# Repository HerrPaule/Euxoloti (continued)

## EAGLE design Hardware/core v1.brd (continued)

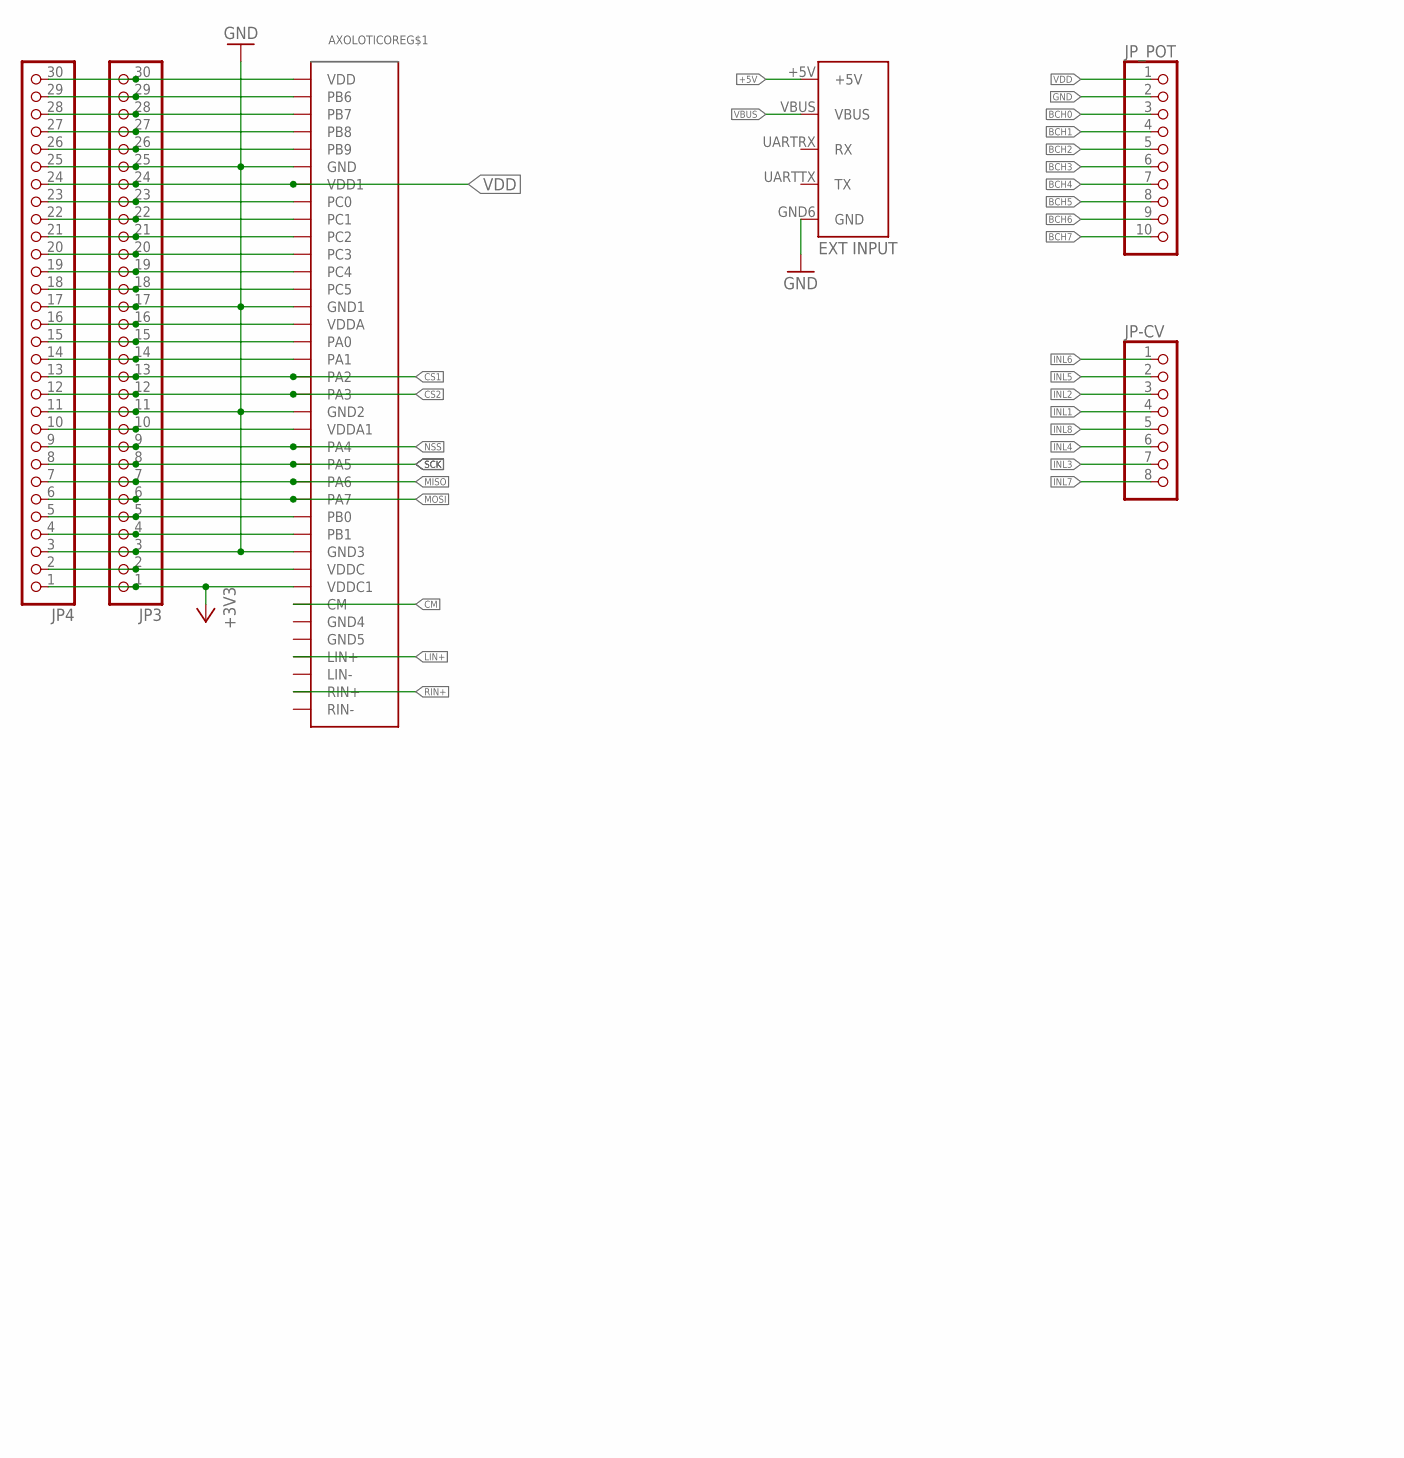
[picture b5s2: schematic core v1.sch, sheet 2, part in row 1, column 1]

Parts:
AXOLOTICORE: AXOLOTI-CORE
JP3, JP4: PINHD-1X30; 1X30
JP-CV: PINHD-1X8_2.54; 1X08
JP_POT: PINHD-1X10; 1X10

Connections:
+3V3: AXOLOTICORE.VDDC1, JP3.1, JP4.1; also elsewhere on the board
+5V: AXOLOTICORE.+5V; also elsewhere on the board
BCH0: JP_POT.3; also elsewhere on the board
BCH1: JP_POT.4; also elsewhere on the board
BCH2: JP_POT.5; also elsewhere on the board
BCH3: JP_POT.6; also elsewhere on the board
BCH4: JP_POT.7; also elsewhere on the board
BCH5: JP_POT.8; also elsewhere on the board
BCH6: JP_POT.9; also elsewhere on the board
BCH7: JP_POT.10; also elsewhere on the board
CM: AXOLOTICORE.CM; also elsewhere on the board
CS1: AXOLOTICORE.PA2, JP3.13, JP4.13; also elsewhere on the board
CS2: AXOLOTICORE.PA3, JP3.12, JP4.12; also elsewhere on the board
GND: AXOLOTICORE.GND, AXOLOTICORE.GND1, AXOLOTICORE.GND2 (GND3), AXOLOTICORE.GND3 (GND2), AXOLOTICORE.GND6 (GND), JP3.3, JP3.11, JP3.17, JP3.25, JP4.3, JP4.11, JP4.17, JP4.25, JP_POT.2; also elsewhere on the board
INL1: JP-CV.4; also elsewhere on the board
INL2: JP-CV.3; also elsewhere on the board
INL3: JP-CV.7; also elsewhere on the board
INL4: JP-CV.6; also elsewhere on the board
INL5: JP-CV.2; also elsewhere on the board
INL6: JP-CV.1; also elsewhere on the board
INL7: JP-CV.8; also elsewhere on the board
INL8: JP-CV.5; also elsewhere on the board
LIN+: AXOLOTICORE.LIN+; also elsewhere on the board
MISO: AXOLOTICORE.PA6, JP3.7, JP4.7; also elsewhere on the board
MOSI: AXOLOTICORE.PA7, JP3.6, JP4.6; also elsewhere on the board
unnamed: AXOLOTICORE.PB1, JP3.4, JP4.4
unnamed: AXOLOTICORE.PB0, JP3.5, JP4.5
unnamed: AXOLOTICORE.VDDC, JP3.2, JP4.2
unnamed: AXOLOTICORE.VDDA1, JP3.10, JP4.10
unnamed: AXOLOTICORE.PA1, JP3.14, JP4.14
unnamed: AXOLOTICORE.PA0, JP3.15, JP4.15
unnamed: AXOLOTICORE.VDDA, JP3.16, JP4.16
unnamed: AXOLOTICORE.PC5, JP3.18, JP4.18
unnamed: AXOLOTICORE.PC4, JP3.19, JP4.19
unnamed: AXOLOTICORE.PC3, JP3.20, JP4.20
unnamed: AXOLOTICORE.PC2, JP3.21, JP4.21
unnamed: AXOLOTICORE.PC1, JP3.22, JP4.22
unnamed: AXOLOTICORE.PC0, JP3.23, JP4.23
unnamed: AXOLOTICORE.PB9, JP3.26, JP4.26
unnamed: AXOLOTICORE.PB8, JP3.27, JP4.27
unnamed: AXOLOTICORE.PB7, JP3.28, JP4.28
unnamed: AXOLOTICORE.PB6, JP3.29, JP4.29
NSS: AXOLOTICORE.PA4, JP3.9, JP4.9
RIN+: AXOLOTICORE.RIN+; also elsewhere on the board
SCK: AXOLOTICORE.PA5, JP3.8, JP4.8; also elsewhere on the board
VBUS: AXOLOTICORE.VBUS; also elsewhere on the board
VDD: AXOLOTICORE.VDD1, JP3.24, JP4.24, JP_POT.1; also elsewhere on the board
VDD+: AXOLOTICORE.VDD, JP3.30, JP4.30

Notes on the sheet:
Paul 2015
contact@irieelectronics.de

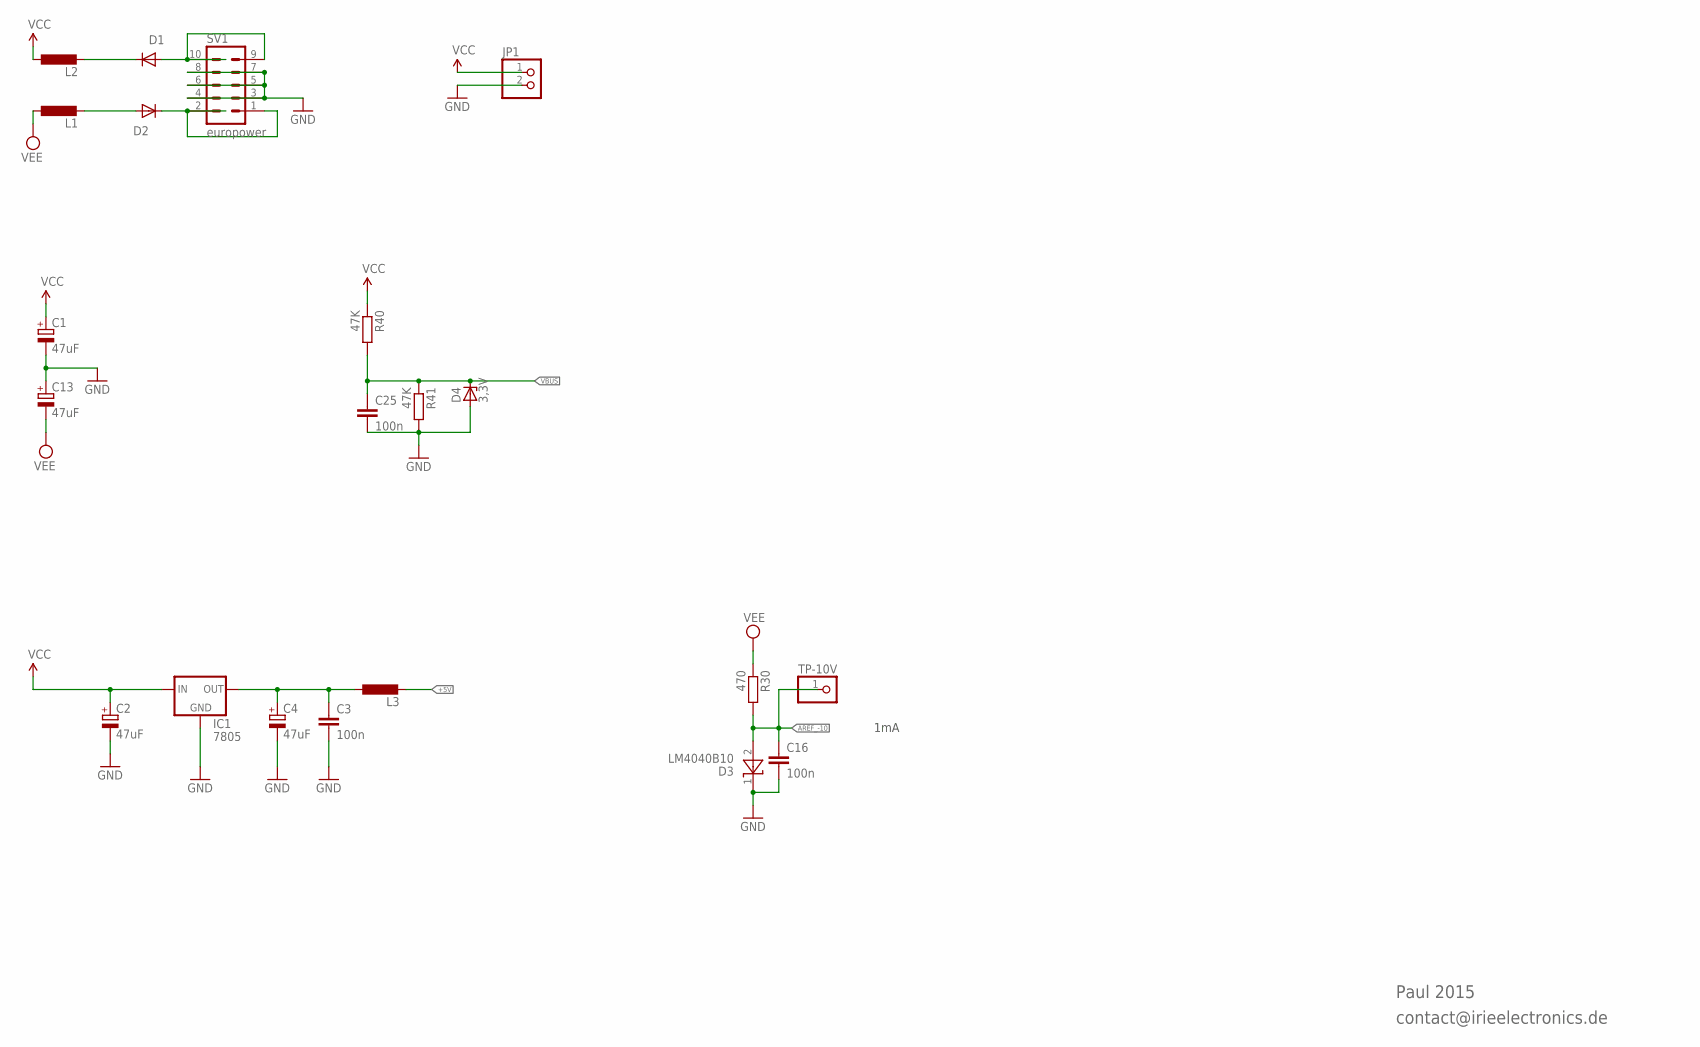
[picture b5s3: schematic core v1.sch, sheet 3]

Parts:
C1, C2, C13: 47uF; E2-5
C3, C16, C25: 100n; C025-025X050
C4: 47uF; E2,5-5
D1, D2: 1N5819HW; DO35-10
D3: LM4040B10; TO-92
D4: 3,3V; DO35Z10
IC1: 7805; 78XXS
JP1: PINHD-1X2; 1X02
L1, L2, L3: L-EU0207/10; 0207/10
R30: 470; 0207/12
R40, R41: 47K; 0207/7
SV1: europower; EURO_PWR_HEADER_FAT
TP-10V: PINHD-1X1_2.54; 1X01

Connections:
+5V: L3.2; also elsewhere on the board
+5V_RAW: C3.1, C4.+, IC1.OUT, L3.1
AREF_-10: C16.1, D3.2 (A), R30.2, TP-10V.1; also elsewhere on the board
GND: C1.-, C2.-, C3.2, C4.-, C13.+, C16.2, C25.2, D3.1 (C), D4.A, IC1.GND, JP1.2, R41.2, SV1.3, SV1.4, SV1.5, SV1.6, SV1.7, SV1.8; also elsewhere on the board
unnamed: D1.C, L2.2
unnamed: D2.A, L1.2
unnamed: D1.A, SV1.9, SV1.10
unnamed: D2.C, SV1.1, SV1.2
VBUS: C25.1, D4.C, R40.2, R41.1; also elsewhere on the board
VCC: C1.+, C2.+, IC1.IN, JP1.1, L2.1, R40.1; also elsewhere on the board
VEE: C13.-, L1.1, R30.1; also elsewhere on the board

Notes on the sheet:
1mA
Paul 2015
contact@irieelectronics.de

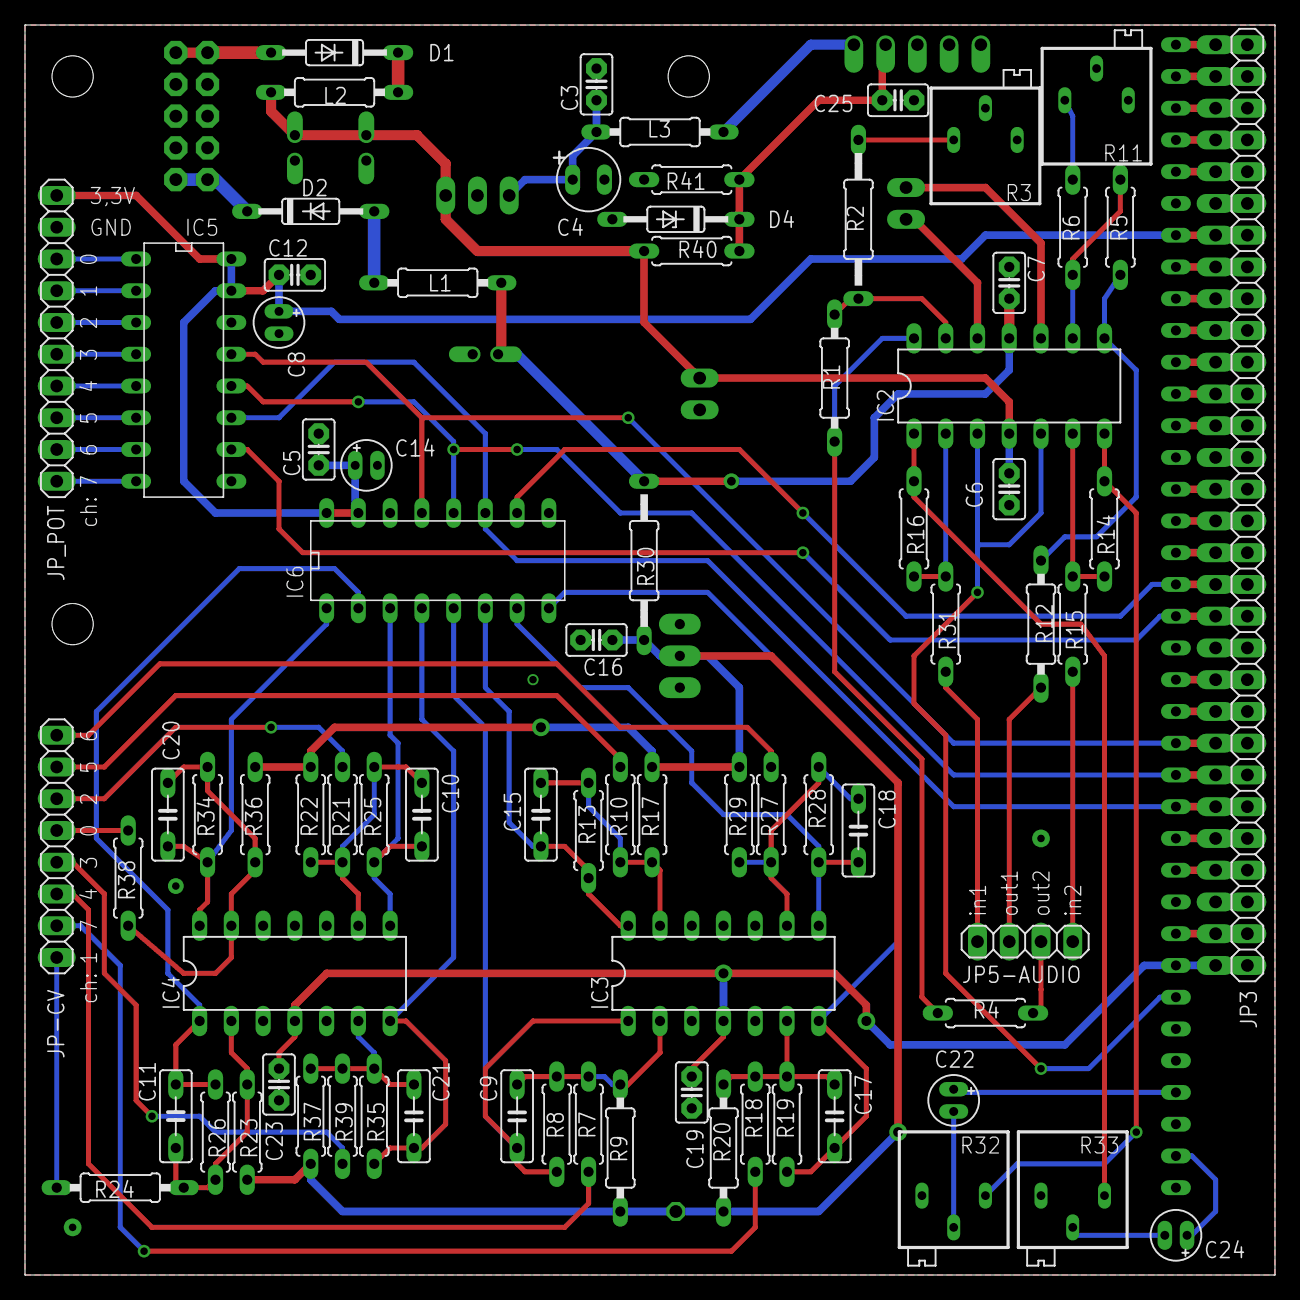
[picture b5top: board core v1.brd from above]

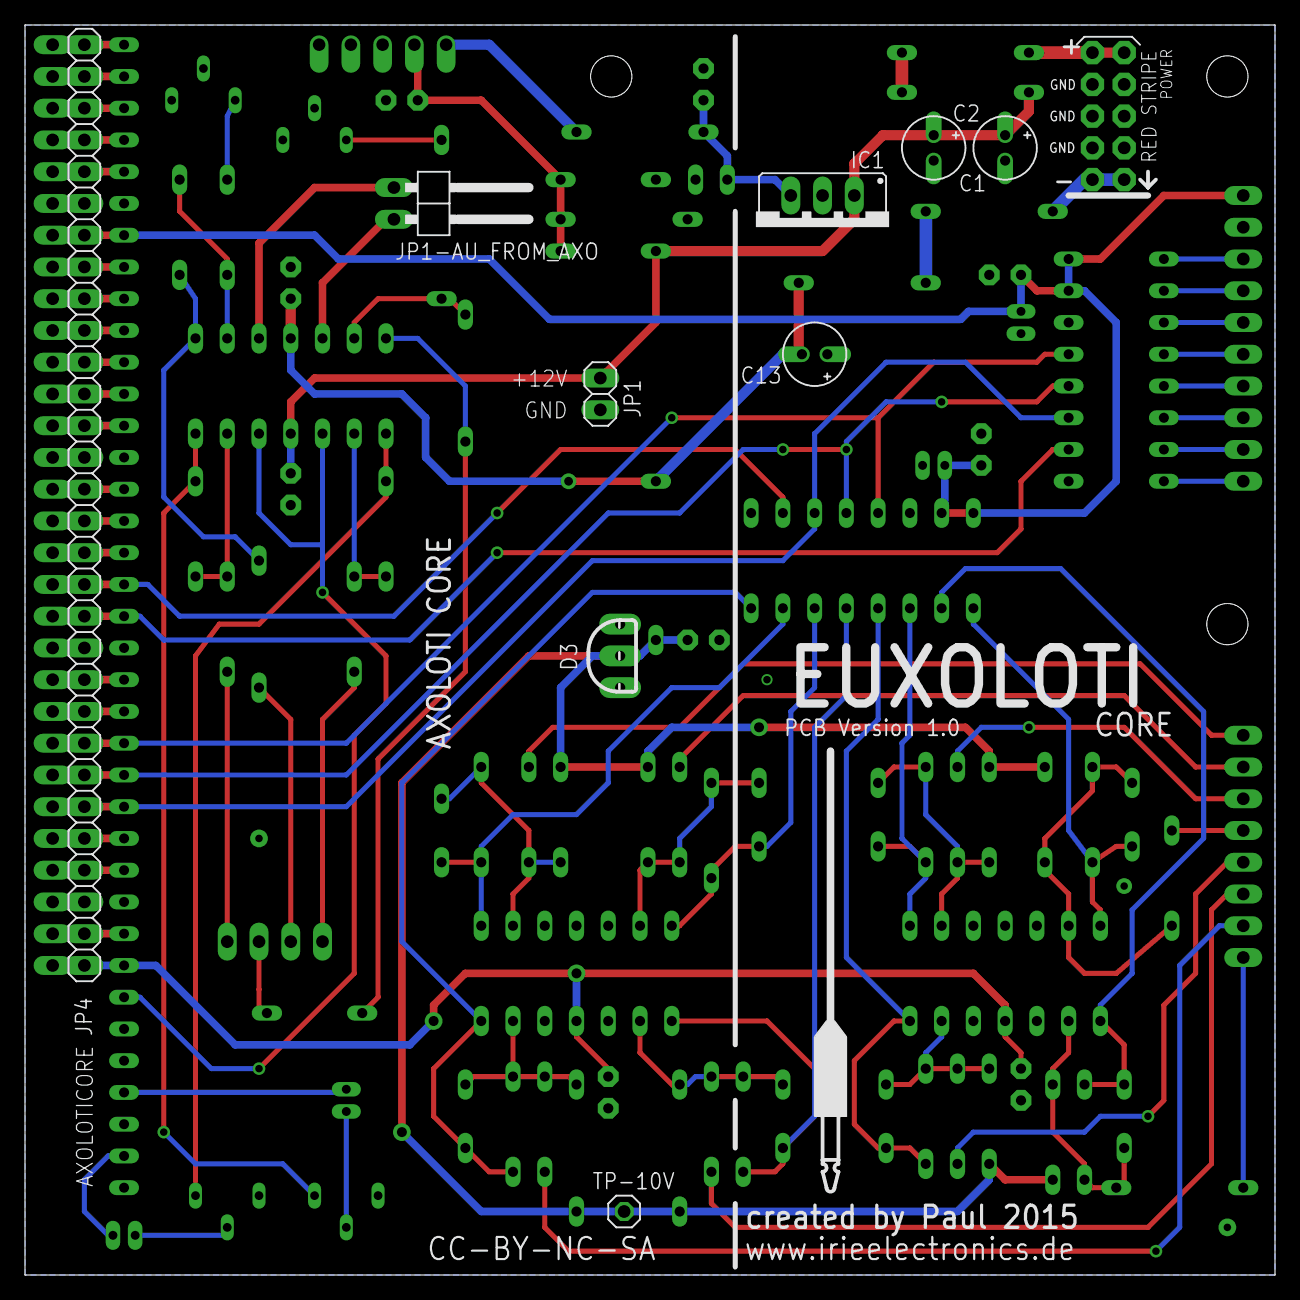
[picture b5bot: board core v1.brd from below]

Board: 4 copper layers, 100.0 x 100.0 mm, 90 parts (12 on the bottom side), 90 nets.

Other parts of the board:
U$1: KLINKENBILD

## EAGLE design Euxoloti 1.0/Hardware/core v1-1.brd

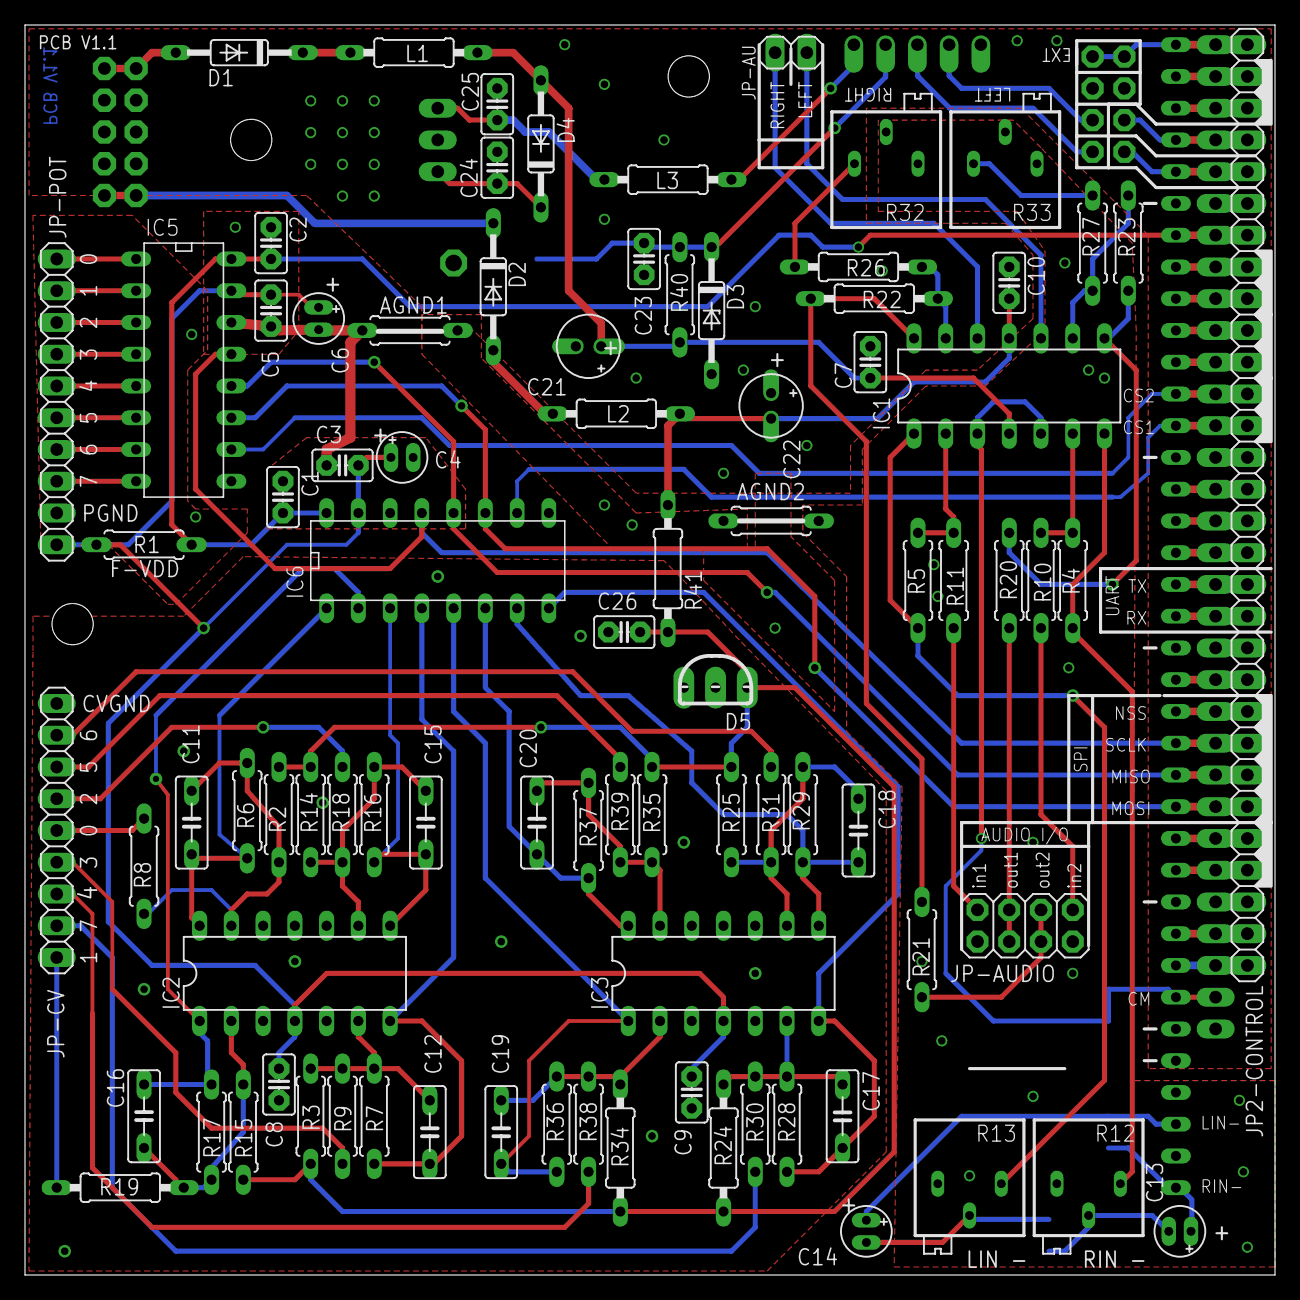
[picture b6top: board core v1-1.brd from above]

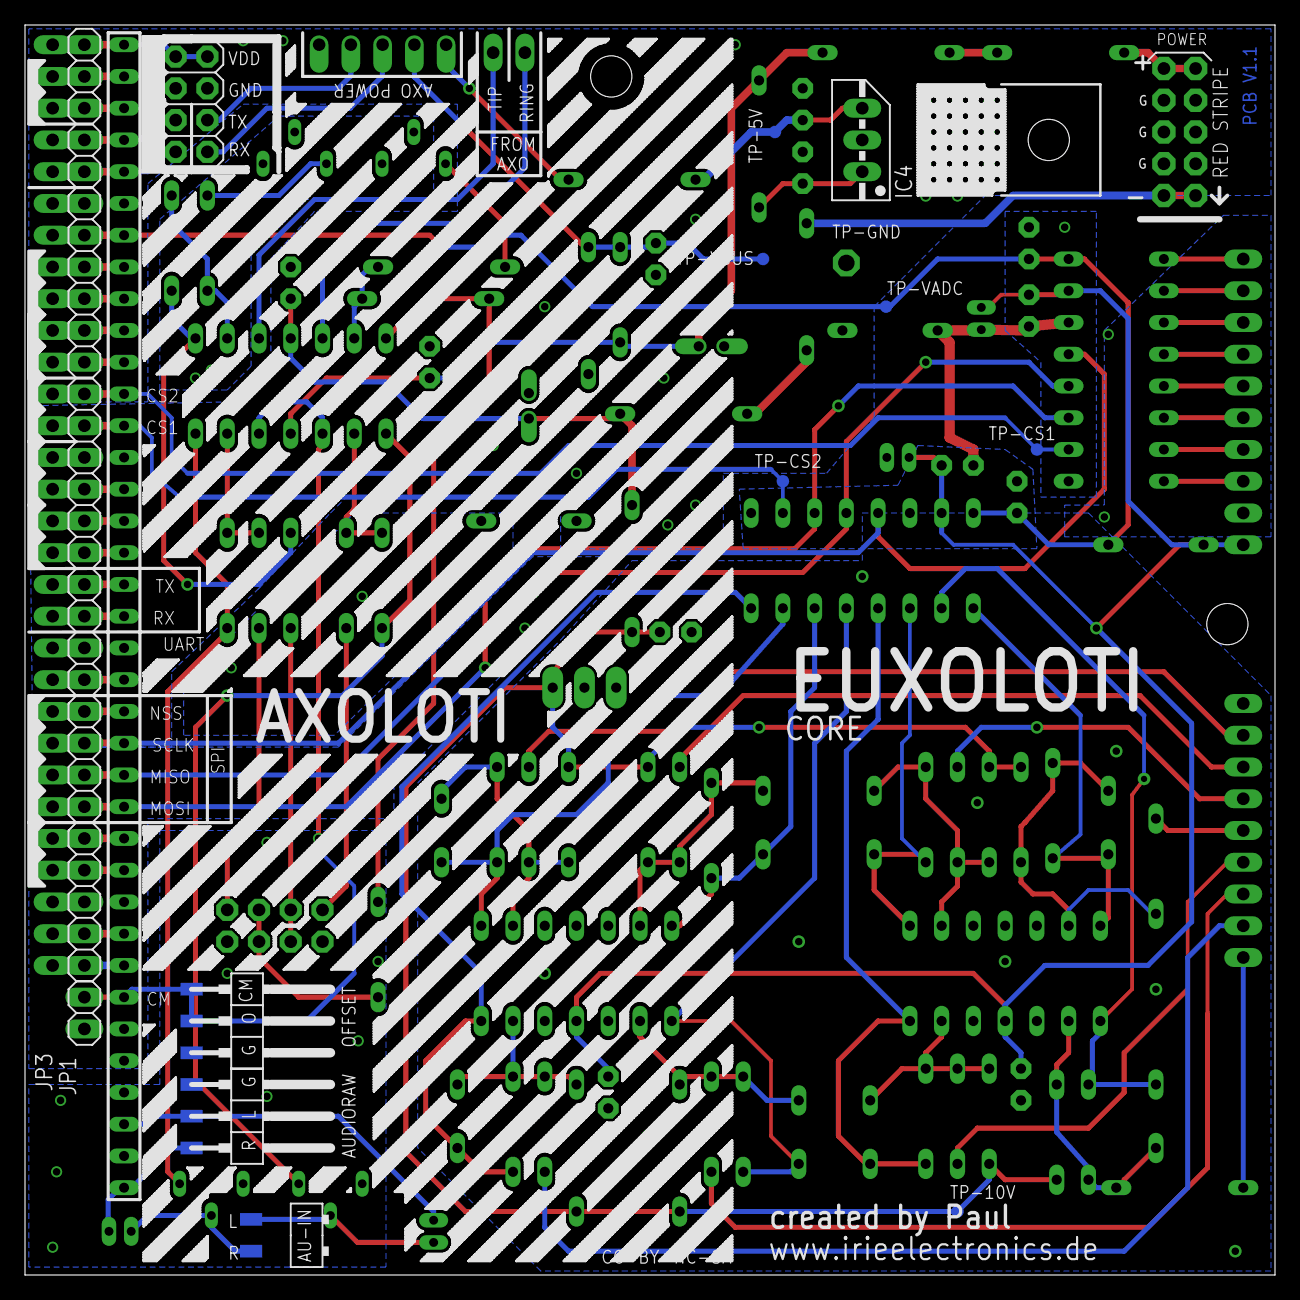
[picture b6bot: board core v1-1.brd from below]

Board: 4 copper layers, 100.0 x 100.0 mm, 104 parts (16 on the bottom side), 96 nets.

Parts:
AGND1, AGND2: 0R; 0207/7
AU-IN: 1X02SMD/90
AUDIORAW: 1X03SMD/90
AXO_CORE: AXO-CORE; AXOLOTI-CORE
BOTTOM_ARTWORK: LABEL_COREBOTTOM
C1, C2, C3, C5, C7, C8, C9, C10, C23, C25, C26: 100n; C025-025X050
C4, C6, C13, C14: 10uF; E1,8-4
C11, C12, C15, C16, C17, C18, C19, C20: 1n; C050-025X075
C21, C22: 47uF; E2-5
C24: 330n; C025-025X050
D1, D2: 1N5819; DO35-10
D3: 3,3V; DO35Z10
D4: 1N5819HW; DO35-10
D5: LM4040A10; TO-92
EXT: 2X04
IC1: TL074P; DIL14
IC2, IC3: MCP6004; DIL14
IC4: 7805; 78MXXS
JP1, JP2-CONTROL: 1X30
JP3: 1X02
JP-AU: 1X02
JP-AUDIO: 2X04
JP-CV: 1X09
JP-POT: 1X10
L1, L2, L3: 0207/10
OFFSET: 1X03SMD/90
POWER: EURO_POWER_HEADERFAT_PADS; EURO_PWR_HEADER_FAT
R1: 10R; 0207/7
R2, R3, R14, R15, R25, R35: 200k; 0207/7
R4, R5, R27: 3,3K; 0207/7
R6, R7, R16, R17, R29, R36, R37: 33K; 0207/7
R8, R9, R18, R30, R31, R38, R39: 100k; 0207/7
R10, R11, R23: 22K; 0207/7
R12, R13: 10K; RTRIM3296P
R19: 100k; 0207/10
R20, R21: 1K; 0207/7
R22: 22K; 0207/10
R24, R34: 200k; 0207/10
R26: 3,3K; 0207/10
R28: 66,5K; 0207/7
R32, R33: 5K; RTRIM3296P
R40: 47K; 0207/7
R41: 470; 0207/10
TP-5V, TP-10V: TPTP10R; TP10R
TP-CS1, TP-CS2: TPTP10R; TP10R
TP-GND: TPPAD1-13; P1-13
TP-VADC: TPTP10R; TP10R
TP-VBUS: TPTP10R; TP10R
U$1, U$2: MCP3208_DIP; MCP2308

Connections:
+3V3: AXO_CORE.VDDC1, JP1.1, JP2-CONTROL.1
+5V: AXO_CORE.+5V, L3.2
+5V_RAW: C25.1, IC4.OUT, L3.1, TP-5V.TP
AREF_-10: C26.1, D5.A, R2.2, R3.2, R14.2, R15.2, R24.2, R25.2, R34.2, R35.2, R41.2, TP-10V.TP
BCH0: JP-POT.1, U$2.P$1
BCH1: JP-POT.2, U$2.P$2
BCH2: JP-POT.3, U$2.P$3
BCH3: JP-POT.4, U$2.P$4
BCH4: JP-POT.5, U$2.P$5
BCH5: JP-POT.6, U$2.P$6
BCH6: JP-POT.7, U$2.P$7
BCH7: JP-POT.8, U$2.P$8
CH0: C11.2, IC2.14, R6.1, U$1.P$1
CH1: C15.2, IC2.8, R16.1, U$1.P$3
CH2: C12.2, IC2.7, R7.1, U$1.P$4
CH3: C16.2, IC2.1, R17.1, U$1.P$2
CH4: C18.2, IC3.8, R29.1, U$1.P$7
CH5: C17.2, IC3.7, R28.1, U$1.P$8
CH6: C19.2, IC3.1, R36.1, U$1.P$5
CH7: C20.2, IC3.14, R37.1, U$1.P$6
CM: AXO_CORE.CM, IC1.3, IC1.5, JP3.1, OFFSET.1, OFFSET.2
CS1: AXO_CORE.PC5, JP1.18, JP2-CONTROL.18, TP-CS2.TP, U$1.P$10
CS2: AXO_CORE.PC4, JP1.19, JP2-CONTROL.19, TP-CS1.TP, U$2.P$10
GND: AGND1.2, AGND2.2, AXO_CORE.GND, AXO_CORE.GND1, AXO_CORE.GND2, AXO_CORE.GND3, AXO_CORE.GND4, AXO_CORE.GND5, AXO_CORE.GND6, C7.2, C10.1, C21.-, C22.+, C23.2, C24.2, C25.2, D3.A, EXT.3, EXT.4, IC4.GND, JP1.3, JP1.11, JP1.17, JP1.25, JP2-CONTROL.3, JP2-CONTROL.11, JP2-CONTROL.17, JP2-CONTROL.25, JP3.2, POWER.3, POWER.4, POWER.5, POWER.6, POWER.7, POWER.8, TP-GND.TP
GNDA: AGND1.1, C1.1, C2.1, C3.2, C4.-, C5.2, C6.-, C8.2, C9.2, C26.2, D5.C, IC2.3, IC2.5, IC2.10, IC2.11, IC2.12, IC3.3, IC3.5, IC3.10, IC3.11, IC3.12, JP-CV.1, JP-POT.9, U$1.P$9, U$1.P$14, U$2.P$9, U$2.P$14
GNDB: AGND2.1, AUDIORAW.1, JP-AUDIO.2, JP-AUDIO.8, OFFSET.3, R12.1, R13.1, R32.1, R32.2, R33.1, R33.2
IN1: JP-AUDIO.1, R10.2
IN2: JP-AUDIO.7, R11.2
INL1: JP-CV.5, R8.2
INL2: JP-CV.4, R18.2
INL3: JP-CV.8, R30.2
INL4: JP-CV.7, R38.2
INL5: JP-CV.3, R39.2
INL6: JP-CV.2, R31.2
INL7: JP-CV.9, R19.2
INL8: JP-CV.6, R9.2
LIN-: AUDIORAW.2, AXO_CORE.LIN-, C14.+
MIDI/RX: AXO_CORE.UARTRX, EXT.8
MIDI/TX: AXO_CORE.UARTTX, EXT.6
MISO: AXO_CORE.PA6, JP1.7, JP2-CONTROL.7, U$1.P$12, U$2.P$12
MOSI: AXO_CORE.PA7, JP1.6, JP2-CONTROL.6, U$1.P$11, U$2.P$11
unnamed: D1.C, L1.2
unnamed: C15.1, IC2.9, R14.1, R16.2, R18.1
unnamed: D2.A, L2.2
unnamed: R26.2, R32.3
unnamed: C16.1, IC2.2, R15.1, R17.2, R19.1
unnamed: IC1.13, R22.2, R26.1
unnamed: IC1.14, R21.2, R22.1
unnamed: AU-IN.2, C13.-, R12.2
unnamed: R27.2, R33.3
unnamed: IC1.9, R23.2, R27.1
unnamed: C11.1, IC2.13, R2.1, R6.2, R8.1
unnamed: IC1.8, R20.2, R23.1
unnamed: IC1.10, JP-AU.2
unnamed: IC1.12, JP-AU.1
unnamed: C12.1, IC2.6, R3.1, R7.2, R9.1
unnamed: AU-IN.1, C14.-, R13.2
unnamed: IC1.6, R4.2, R10.1
unnamed: C19.1, IC3.2, R34.1, R36.2, R38.1
unnamed: IC1.7, R4.1, R12.3
unnamed: C20.1, IC3.13, R35.1, R37.2, R39.1
unnamed: IC1.2, R5.2, R11.1
unnamed: C17.1, IC3.6, R24.1, R28.2, R30.1
unnamed: IC1.1, R5.1, R13.3
unnamed: C18.1, IC3.9, R25.1, R29.2, R31.1
unnamed: C24.1, D4.C, IC4.IN
unnamed: AXO_CORE.VDDC, JP1.2, JP2-CONTROL.2
unnamed: AXO_CORE.VDDA1, JP1.10, JP2-CONTROL.10
unnamed: AXO_CORE.VDDA, JP1.16, JP2-CONTROL.16
unnamed: AXO_CORE.PC3, JP1.20, JP2-CONTROL.20
unnamed: AXO_CORE.PC2, JP1.21, JP2-CONTROL.21
unnamed: AXO_CORE.PC1, JP1.22, JP2-CONTROL.22
unnamed: AXO_CORE.PC0, JP1.23, JP2-CONTROL.23
unnamed: AXO_CORE.PB7, JP1.28, JP2-CONTROL.28
unnamed: AXO_CORE.PB6, JP1.29, JP2-CONTROL.29
unnamed: D1.A, POWER.9, POWER.10
unnamed: D2.C, POWER.1, POWER.2
NSS: AXO_CORE.PA4, JP1.9, JP2-CONTROL.9
OUT1: JP-AUDIO.3, JP-AUDIO.4, R21.1
OUT2: JP-AUDIO.5, JP-AUDIO.6, R20.1
PA0/PWM: AXO_CORE.PA0, JP1.15, JP2-CONTROL.15
PA1/PWM: AXO_CORE.PA1, JP1.14, JP2-CONTROL.14
PA2/TX: AXO_CORE.PA2, JP1.13, JP2-CONTROL.13
PA3/RX: AXO_CORE.PA3, JP1.12, JP2-CONTROL.12
PB0/PWM: AXO_CORE.PB0, JP1.5, JP2-CONTROL.5
PB1/PWM: AXO_CORE.PB1, JP1.4, JP2-CONTROL.4
RIN-: AUDIORAW.3, AXO_CORE.RIN-, C13.+
SCK: AXO_CORE.PA5, JP1.8, JP2-CONTROL.8, U$1.P$13, U$2.P$13
SCL: AXO_CORE.PB8, EXT.5, JP1.27, JP2-CONTROL.27
SDA: AXO_CORE.PB9, EXT.7, JP1.26, JP2-CONTROL.26
VBUS: AXO_CORE.VBUS, C23.1, D3.C, R40.2, TP-VBUS.TP
VCC: C7.1, C21.+, D4.A, IC1.4, L1.1, R40.1
VDD: AXO_CORE.VDD1, C1.2, C2.2, JP1.24, JP2-CONTROL.24, R1.1, TP-VADC.TP, U$1.P$16, U$2.P$16
VDD+: AXO_CORE.VDD, EXT.1, EXT.2, JP1.30, JP2-CONTROL.30
VDDAA: C3.1, C4.+, C5.1, C6.+, C8.1, C9.1, IC2.4, IC3.4, JP-POT.10, R1.2, U$1.P$15, U$2.P$15
VEE: C10.2, C22.-, IC1.11, L2.1, R41.1

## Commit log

2015-12-31 illustrator file
2015-12-31 eagle files
2015-12-31 core schematic
2016-01-01 BOM PCB VERSION 1.00
2016-01-04 correct values
2016-01-20 update REV 2
2016-01-20 schematic pdf rev2
2016-02-12 Rename readme.me to README.md
2016-02-20 special note from toneburst
2016-02-27 calibration file
2016-02-27 patch
2016-02-28 Expanders
2016-03-02 TEST DAC8552 16bit SPI
2016-03-05 axoloti encoder patch
2016-03-06 LED DOT MATRIX (SPI & MAX7219)
2016-03-16 Teenage Engineering PO-12 sync to Axoloti
2016-03-17 MPR121 & axoloti
2016-06-12 serial communication example
2016-09-23 euxoloti 1.2 update
2016-10-06 Euxoloti 1.2/Axoloti audio calibration
2016-10-29 BOMs update
2016-10-29 update part numbers
2016-11-06 now compatible with latest Axo patcher
2016-11-07 midi receive by serial port 2 script
2017-02-12 updated script file (check new object "button_pot_led")
2017-02-22 changes for new objects
